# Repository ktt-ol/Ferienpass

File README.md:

# Ferienpass

## Submodules
We use the [kicad-ESP8266][kicadESP8266Lib] Libary form [jdunmire][ESP8266LibAuthor].

To clone the whole Repository including the submodules simpy use the `--recusive` Option or run the Commands `git submodule init && git submodule update` inside this repository adter cloning.

[kicadESP8266Lib]: https://github.com/jdunmire/kicad-ESP8266
[ESP8266LibAuthor]: https://github.com/jdunmire

## Arduino Library
Install the following librarys via the Arduino IDE:
- Adafruit BME280 Library
- Adafruit GFX LIbrary
- Adafruit NeoPixel
- Adafruit Unified Sensor
- ACROBOTIC SSD1306

Modify three lib-files (first two for I2C):
- Adafruit_BME280.h: Line 32: Change `BME280_ADDRESS` from `0x77` to `0x76`
- Adafruit_BME280.cpp: Line 50: Change `Wire.begin();` to `Wire.begin(5, 4); // Pin D1, D2 of ESP`
- Adafruit_SSD1306.h: Line 73/74: use line 73 `#define SSD1306_128_64`  instead of line 74 `#define SSD1306_128_32`

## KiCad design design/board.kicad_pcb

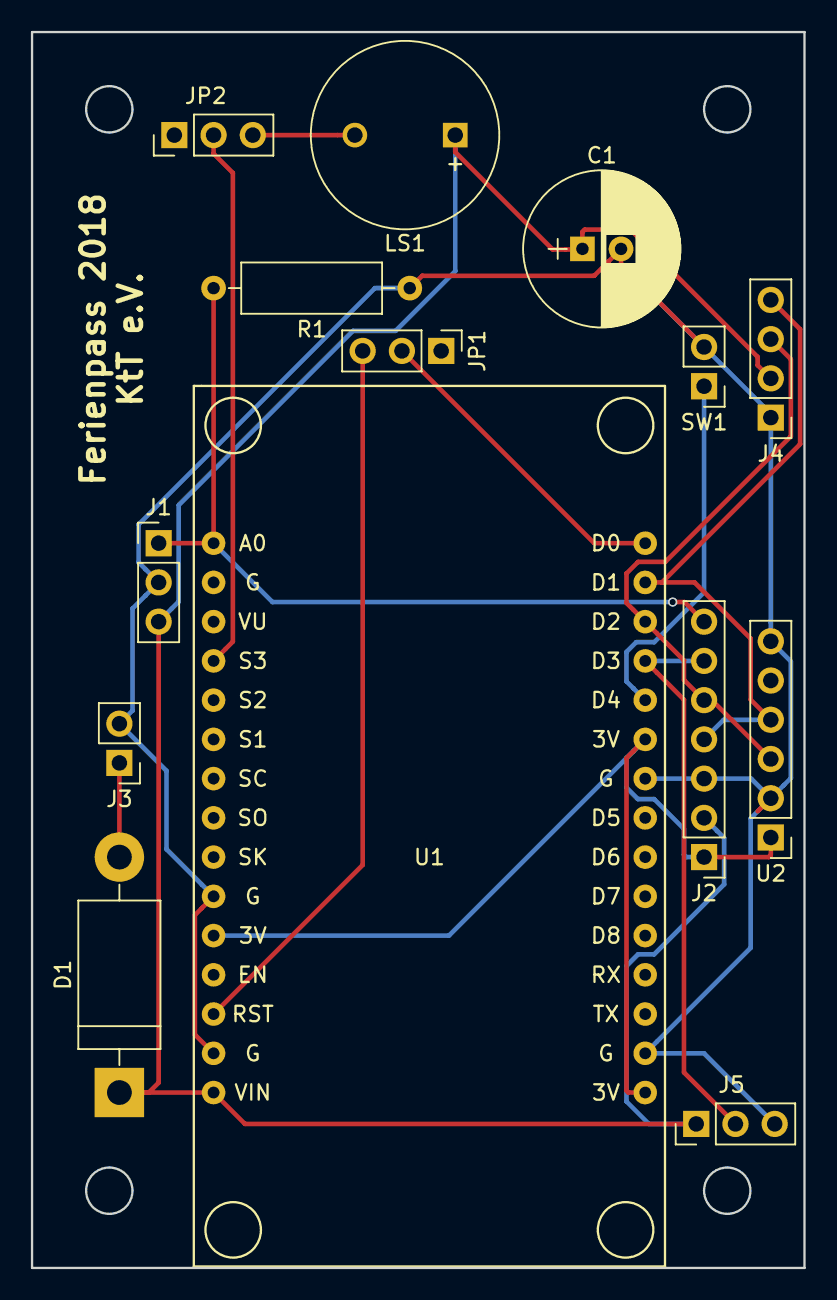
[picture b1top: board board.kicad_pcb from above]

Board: 2 copper layers, 50.0 x 80.0 mm, 14 parts (0 on the bottom side), 13 nets.

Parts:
C1: 2200µF; CP_Radial_D10.0mm_P2.50mm
D1: D; D_DO-201AD_P15.24mm_Horizontal
J1: Mic; Socket_Strip_Straight_1x03_Pitch2.54mm
J2: DEBUG_CONN; Socket_Strip_Straight_1x07_Pitch2.54mm
J3: PWR_CONN; Pin_Header_Straight_1x02_Pitch2.54mm
J4: 0.97" OLED; Socket_Strip_Straight_1x04_Pitch2.54mm
J5: WS2812b; Socket_Strip_Straight_1x03_Pitch2.54mm
JP1: DSLEEP_JUMP; Pin_Header_Straight_1x03_Pitch2.54mm
JP2: BEEPER_JUMP; Pin_Header_Straight_1x03_Pitch2.54mm
LS1: Speaker; MagneticBuzzer_ProSignal_ABT-410-RC
R1: 10K; R_Axial_DIN0309_L9.0mm_D3.2mm_P12.70mm_Horizontal
SW1: SW_Push; Socket_Strip_Straight_1x02_Pitch2.54mm
U1: NodeMCU1.0(ESP-12E); NodeMCU1.0(12-E)
U2: BME280; Socket_Strip_Straight_1x06_Pitch2.54mm

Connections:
+3V3: J2.1, U1.11, U1.16, U1.25, U2.1
D0: JP1.2, U1.30
GND: C1.2, J1.2, J2.3, J3.2, J4.1, J5.3, R1.1, SW1.2, U1.10, U1.14, U1.17, U1.24, U2.2, U2.6
MIC: J1.1, J2.7, R1.2, U1.1
unnamed: D1.2, J3.1
unnamed: JP1.3, U1.13
unnamed: JP2.3, LS1.2
unnamed: SW1.1, U1.26
SCL: J2.5, J4.3, U1.28, U2.3
SD3: JP2.2, U1.4
SDA: J2.4, J4.4, U1.29, U2.4
VCC: C1.1, D1.1, J1.3, J2.2, J4.2, J5.1, LS1.1, U1.15
WS2812b: J2.6, J5.2, U1.27

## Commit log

2017-02-18 initial sensor framework for esp8266
2017-02-18 sensor class
2017-02-18 test programm for bme280 sensor
2017-04-08 added Klasse zum anzeigen
2017-04-08 design and main testprogramm
2017-04-15 ws2812b Anschluss auf dem Schaltplan hinzugefügt
2017-04-23 ESP2866 Libary for KiCAD is now a Submodule
2017-04-23 Improvement of README.md
2017-05-05 Schaltplan aktualisiert und erweitert
2017-05-05 fixed bme sensor init, add led and display example
2017-05-05 main
2017-05-06 show wlans and sensor values on oled display
2017-05-12 beeper, fixed wlans on display
2017-05-12 modified and refresched
2017-05-12 microphone support
2017-05-16 finalizing PCB Layout
2017-05-18 added some Text on Silkscreen and some holes
2017-05-19 finalizied board layout
2017-06-06 correction of the Nodemcu Footprint
2017-06-20 Added: Präsentation
2017-06-20 praesentation
2017-06-20 praesentation sensor
2017-06-20 button interrupt fixed
2017-06-24 led brightness
2017-06-26 led number and presi
2017-06-26 daniel
2017-06-26 teilnehmer
2017-06-30 teilnehmer code
2017-06-30 boardv2
2017-06-30 add necessary libs
2018-01-20 improved PCB-Layout for next Year
2018-01-20 optimized microphone logic
